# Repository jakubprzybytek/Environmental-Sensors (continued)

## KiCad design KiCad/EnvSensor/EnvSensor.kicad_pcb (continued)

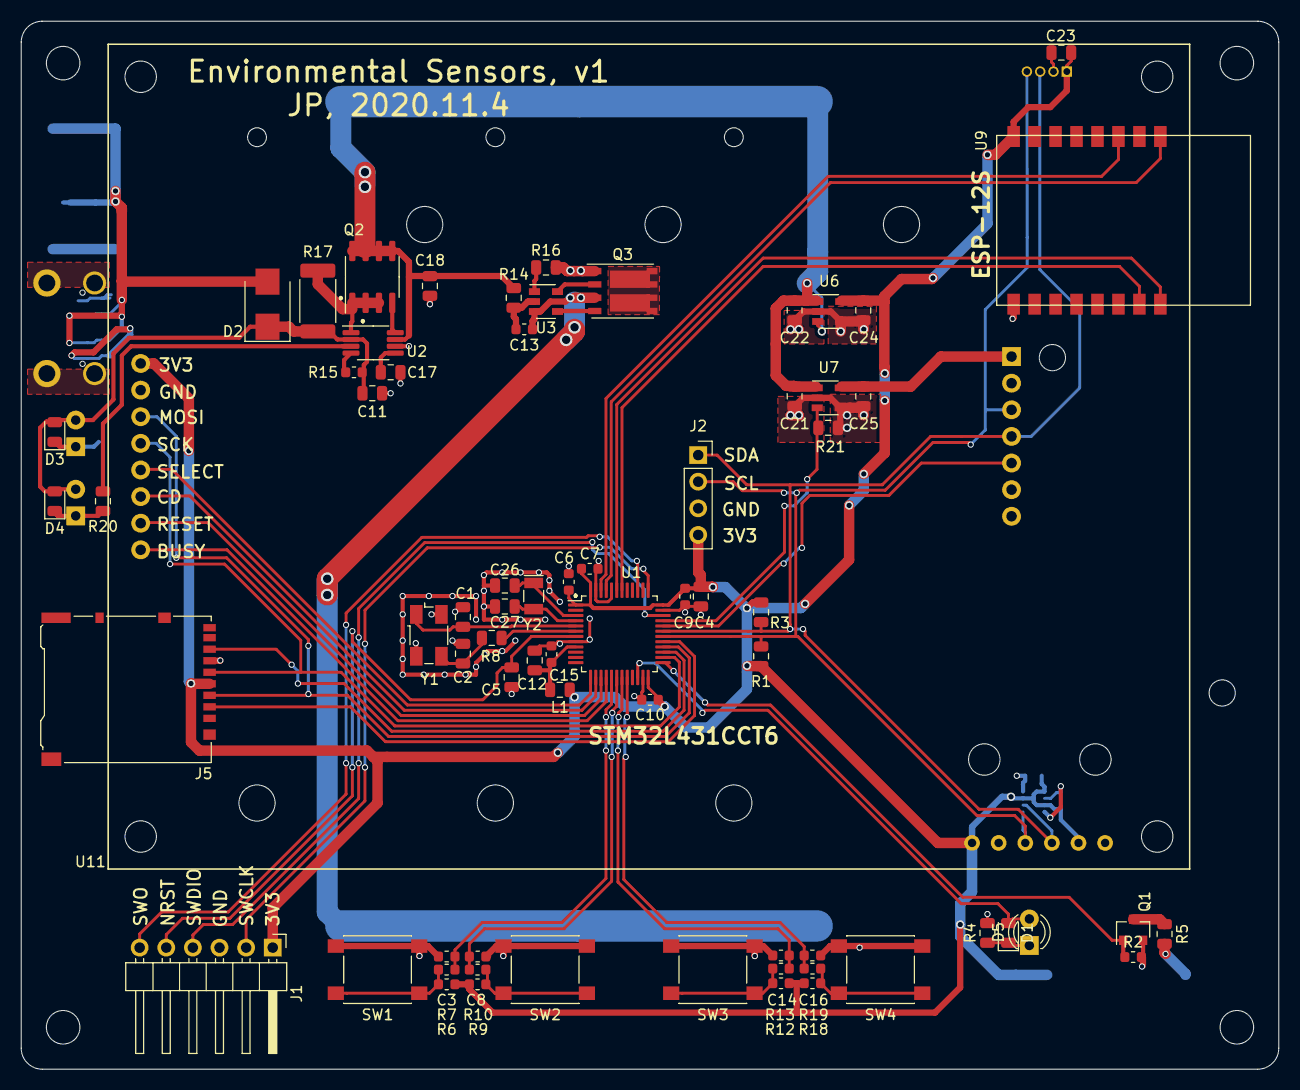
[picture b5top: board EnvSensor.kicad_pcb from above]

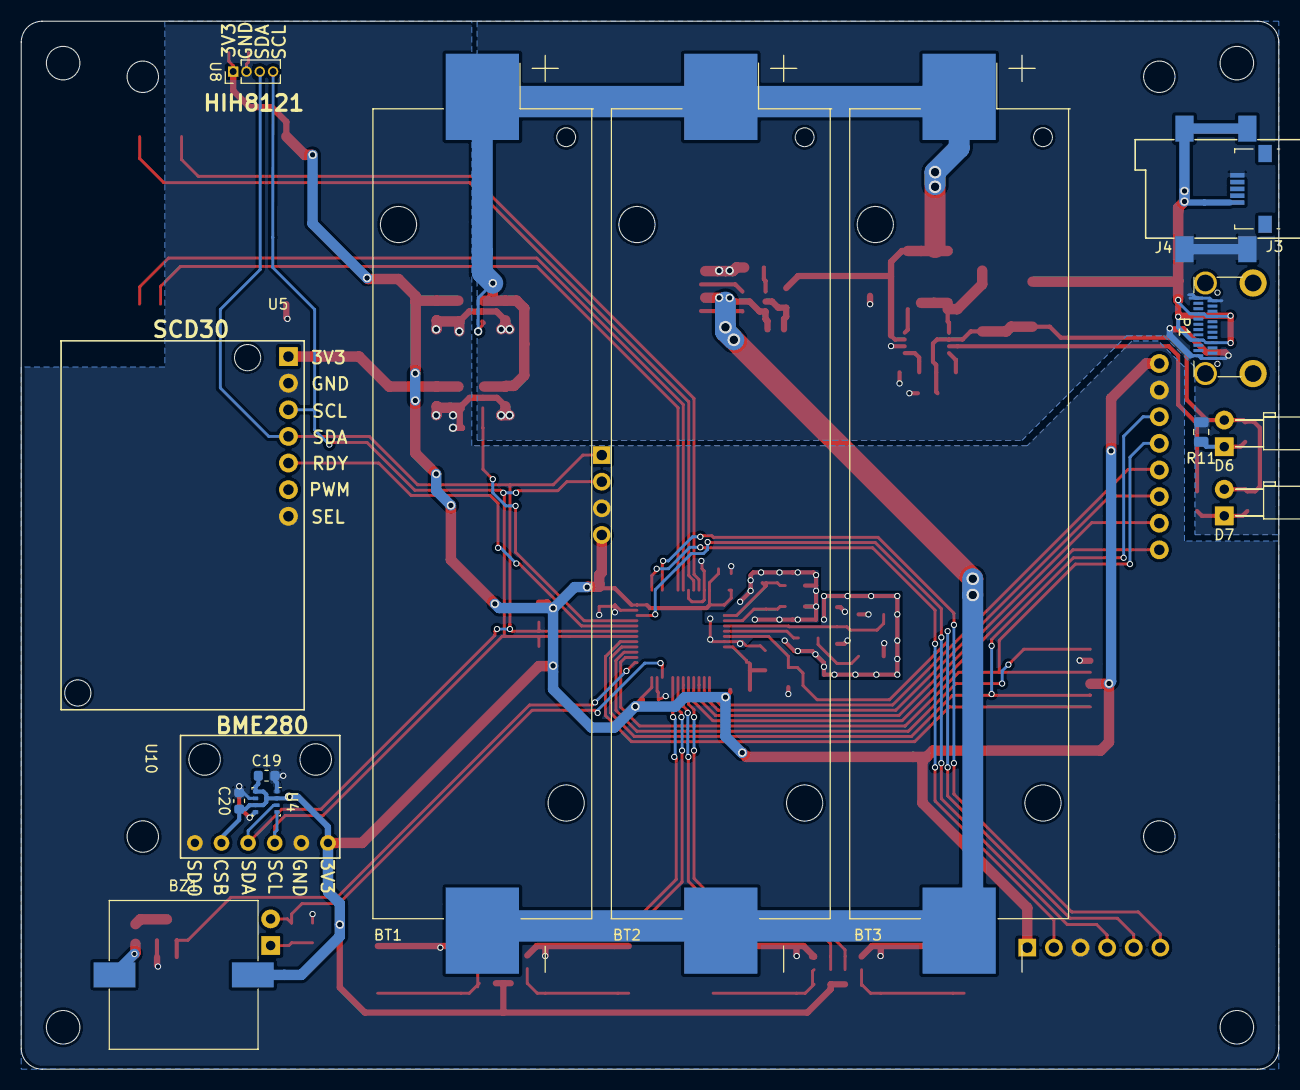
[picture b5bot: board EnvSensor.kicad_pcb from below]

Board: 2 copper layers, 120.0 x 100.0 mm, 90 parts (16 on the bottom side), 58 nets.

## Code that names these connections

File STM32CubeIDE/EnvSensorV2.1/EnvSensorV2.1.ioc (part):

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Mcu.Name=STM32L451R(C-E)Tx
Mcu.Package=LQFP64
Mcu.UserName=STM32L451RETx
PA0.GPIOParameters=GPIO_Label
PA0.GPIO_Label=BATTERY_MEASURE_INPUT
PA0.Signal=ADCx_IN5
PA10.Mode=I2C
PA10.Signal=I2C1_SDA
PA11.GPIOParameters=PinState,GPIO_Label
PA11.GPIO_Label=SDIO_POWER_ENABLE
PA11.PinState=GPIO_PIN_RESET
PA11.Signal=GPIO_Output
PA12.GPIOParameters=GPIO_PuPd,GPIO_Label
PA12.GPIO_Label=SDIO_DETECT
PA12.GPIO_PuPd=GPIO_PULLUP
PA12.Signal=GPIO_Input
PA13\ (JTMS/SWDIO).Mode=Trace_Asynchronous_SW
PA13\ (JTMS/SWDIO).Signal=SYS_JTMS-SWDIO
PA14\ (JTCK/SWCLK).Mode=Trace_Asynchronous_SW
PA14\ (JTCK/SWCLK).Signal=SYS_JTCK-SWCLK
PA2.Mode=Asynchronous
PA2.Signal=USART2_TX
PA3.Mode=Asynchronous
PA3.Signal=USART2_RX
PA5.Mode=TX_Only_Simplex_Unidirect_Master
PA5.Signal=SPI1_SCK
PA7.Mode=TX_Only_Simplex_Unidirect_Master
PA7.Signal=SPI1_MOSI
PA8.GPIOParameters=GPIO_Label
PA8.GPIO_Label=SCD30_READY
PA8.Signal=GPXTI8
PA9.Mode=I2C
PA9.Signal=I2C1_SCL
PB0.GPIOParameters=GPIO_Label
PB0.GPIO_Label=E_INK_RESET
PB0.Signal=GPIO_Output
PB1.GPIOParameters=GPIO_Label
PB1.GPIO_Label=E_INK_BUSY
PB1.Signal=GPXTI1
PB12.GPIOParameters=GPIO_Label
PB12.GPIO_Label=SWITCH_1
PB12.Signal=GPXTI12
PB13.GPIOParameters=GPIO_Label
PB13.GPIO_Label=SWITCH_2
PB13.Signal=GPXTI13
PB14.GPIOParameters=GPIO_Label
PB14.GPIO_Label=SWITCH_3
PB14.Signal=GPXTI14
PB15.GPIOParameters=GPIO_Label
PB15.GPIO_Label=SWITCH_4
PB15.Signal=GPXTI15
PB2.GPIOParameters=PinState,GPIO_Label
PB2.GPIO_Label=POWER_5V_ENABLE
PB2.PinState=GPIO_PIN_RESET
PB2.Signal=GPIO_Output
PB3\ (JTDO/TRACESWO).Mode=Trace_Asynchronous_SW
PB3\ (JTDO/TRACESWO).Signal=SYS_JTDO-SWO
PC0.GPIOParameters=GPIO_Label
PC0.GPIO_Label=LED_4
PC0.Signal=GPIO_Output
PC1.GPIOParameters=GPIO_Label
PC1.GPIO_Label=LED_3
PC1.Signal=GPIO_Output
PC10.GPIOParameters=GPIO_PuPd,GPIO_Speed_High_Default
PC10.GPIO_PuPd=GPIO_PULLUP
PC10.GPIO_Speed_High_Default=GPIO_SPEED_FREQ_LOW
PC10.Mode=SD_4_bits_Wide_bus
PC10.Signal=SDMMC1_D2
PC11.GPIOParameters=GPIO_PuPd,GPIO_Speed_High_Default
PC11.GPIO_PuPd=GPIO_PULLUP
PC11.GPIO_Speed_High_Default=GPIO_SPEED_FREQ_LOW
PC11.Mode=SD_4_bits_Wide_bus
PC11.Signal=SDMMC1_D3
PC12.GPIOParameters=GPIO_Speed_High_Default
PC12.GPIO_Speed_High_Default=GPIO_SPEED_FREQ_LOW
PC12.Mode=SD_4_bits_Wide_bus
PC12.Signal=SDMMC1_CK
PC14-OSC32_IN\ (PC14).Mode=LSE-External-Oscillator
PC14-OSC32_IN\ (PC14).Signal=RCC_OSC32_IN
PC15-OSC32_OUT\ (PC15).Mode=LSE-External-Oscillator
PC15-OSC32_OUT\ (PC15).Signal=RCC_OSC32_OUT
PC2.GPIOParameters=GPIO_Label
PC2.GPIO_Label=LED_2
PC2.Signal=GPIO_Output
PC3.GPIOParameters=GPIO_Label
PC3.GPIO_Label=LED_1
PC3.Signal=GPIO_Output
PC4.GPIOParameters=GPIO_Label
PC4.GPIO_Label=E_INK_SELECT
PC4.Signal=GPIO_Output
PC5.GPIOParameters=GPIO_Speed,GPIO_Label
PC5.GPIO_Label=E_INK_DC
PC5.GPIO_Speed=GPIO_SPEED_FREQ_HIGH
PC5.Signal=GPIO_Output
PC6.GPIOParameters=GPIO_Label
PC6.GPIO_Label=BATTERY_MEASURE_ENABLE
PC6.Signal=GPIO_Output
PC8.GPIOParameters=GPIO_Speed_High_Default
PC8.GPIO_Speed_High_Default=GPIO_SPEED_FREQ_LOW
PC8.Mode=SD_4_bits_Wide_bus
PC8.Signal=SDMMC1_D0
PC9.GPIOParameters=GPIO_Speed_High_Default
PC9.GPIO_Speed_High_Default=GPIO_SPEED_FREQ_LOW
PC9.Mode=SD_4_bits_Wide_bus
PC9.Signal=SDMMC1_D1
PD2.GPIOParameters=GPIO_PuPd,GPIO_Speed_High_Default
PD2.GPIO_PuPd=GPIO_PULLUP
PD2.GPIO_Speed_High_Default=GPIO_SPEED_FREQ_LOW
PD2.Mode=SD_4_bits_Wide_bus
PD2.Signal=SDMMC1_CMD
PH0-OSC_IN\ (PH0).Mode=HSE-External-Oscillator
PH0-OSC_IN\ (PH0).Signal=RCC_OSC_IN
PH1-OSC_OUT\ (PH1).Mode=HSE-External-Oscillator
PH1-OSC_OUT\ (PH1).Signal=RCC_OSC_OUT
RCC.HSE_VALUE=16000000
RCC.SYSCLKFreq_VALUE=16000000
RCC.SYSCLKSource=RCC_SYSCLKSOURCE_HSE
board=custom

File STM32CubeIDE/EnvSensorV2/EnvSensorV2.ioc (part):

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Mcu.Name=STM32L451R(C-E)Tx
Mcu.Package=LQFP64
Mcu.UserName=STM32L451RCTx
PA0.GPIOParameters=GPIO_Label
PA0.GPIO_Label=BATTERY_MEASURE_INPUT
PA0.Signal=ADCx_IN5
PA1.Signal=GPIO_Analog
PA10.Mode=I2C
PA10.Signal=I2C1_SDA
PA13\ (JTMS/SWDIO).Mode=Trace_Asynchronous_SW
PA13\ (JTMS/SWDIO).Signal=SYS_JTMS-SWDIO
PA14\ (JTCK/SWCLK).Mode=Trace_Asynchronous_SW
PA14\ (JTCK/SWCLK).Signal=SYS_JTCK-SWCLK
PA2.Mode=Asynchronous
PA2.Signal=USART2_TX
PA3.Mode=Asynchronous
PA3.Signal=USART2_RX
PA5.Mode=TX_Only_Simplex_Unidirect_Master
PA5.Signal=SPI1_SCK
PA7.Mode=TX_Only_Simplex_Unidirect_Master
PA7.Signal=SPI1_MOSI
PA8.GPIOParameters=GPIO_PuPd,GPIO_Label
PA8.GPIO_Label=SCD30_READY
PA8.GPIO_PuPd=GPIO_NOPULL
PA8.Signal=GPXTI8
PA9.Mode=I2C
PA9.Signal=I2C1_SCL
PB0.GPIOParameters=GPIO_Label
PB0.GPIO_Label=E_INK_RESET
PB0.Signal=GPIO_Output
PB1.GPIOParameters=GPIO_Label
PB1.GPIO_Label=E_INK_BUSY
PB1.Signal=GPXTI1
PB12.GPIOParameters=GPIO_Label
PB12.GPIO_Label=SWITCH_1
PB12.Signal=GPXTI12
PB13.GPIOParameters=GPIO_Label
PB13.GPIO_Label=SWITCH_2
PB13.Signal=GPXTI13
PB14.GPIOParameters=GPIO_Label
PB14.GPIO_Label=SWITCH_3
PB14.Signal=GPXTI14
PB15.GPIOParameters=GPIO_Label
PB15.GPIO_Label=SWITCH_4
PB15.Signal=GPXTI15
PB2.GPIOParameters=PinState,GPIO_Label
PB2.GPIO_Label=POWER_5V_ENABLE
PB2.PinState=GPIO_PIN_SET
PB2.Signal=GPIO_Output
PB3\ (JTDO/TRACESWO).Mode=Trace_Asynchronous_SW
PB3\ (JTDO/TRACESWO).Signal=SYS_JTDO-SWO
PB5.GPIOParameters=GPIO_Label
PB5.GPIO_Label=BATTERY_MEASURE_ENABLE
PB5.Signal=GPIO_Output
PB6.Signal=GPIO_Analog
PB8.GPIOParameters=GPIO_Label
PB8.GPIO_Label=SDIO_DETECT
PB8.Signal=GPIO_Input
PB9.GPIOParameters=GPIO_Label
PB9.GPIO_Label=SDIO_POWER_ENABLE
PB9.Signal=GPIO_Output
PC0.GPIOParameters=GPIO_Label
PC0.GPIO_Label=LED_4
PC0.Signal=GPIO_Output
PC1.GPIOParameters=GPIO_Label
PC1.GPIO_Label=LED_3
PC1.Signal=GPIO_Output
PC10.Mode=SD_4_bits_Wide_bus
PC10.Signal=SDMMC1_D2
PC11.Mode=SD_4_bits_Wide_bus
PC11.Signal=SDMMC1_D3
PC12.Mode=SD_4_bits_Wide_bus
PC12.Signal=SDMMC1_CK
PC2.GPIOParameters=GPIO_Label
PC2.GPIO_Label=LED_2
PC2.Signal=GPIO_Output
PC3.GPIOParameters=GPIO_Label
PC3.GPIO_Label=LED_1
PC3.Signal=GPIO_Output
PC4.GPIOParameters=GPIO_Label
PC4.GPIO_Label=E_INK_SELECT
PC4.Signal=GPIO_Output
PC5.GPIOParameters=GPIO_Speed,GPIO_Label
PC5.GPIO_Label=E_INK_DC
PC5.GPIO_Speed=GPIO_SPEED_FREQ_HIGH
PC5.Signal=GPIO_Output
PC8.Mode=SD_4_bits_Wide_bus
PC8.Signal=SDMMC1_D0
PC9.Mode=SD_4_bits_Wide_bus
PC9.Signal=SDMMC1_D1
PD2.Mode=SD_4_bits_Wide_bus
PD2.Signal=SDMMC1_CMD
PH0-OSC_IN\ (PH0).Mode=HSE-External-Oscillator
PH0-OSC_IN\ (PH0).Signal=RCC_OSC_IN
PH1-OSC_OUT\ (PH1).Mode=HSE-External-Oscillator
PH1-OSC_OUT\ (PH1).Signal=RCC_OSC_OUT
RCC.HSE_VALUE=16000000
board=custom

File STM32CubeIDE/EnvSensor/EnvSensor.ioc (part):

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Mcu.Name=STM32L431C(B-C)Tx
Mcu.Package=LQFP48
Mcu.UserName=STM32L431CCTx
PA10.Mode=I2C
PA10.Signal=I2C1_SDA
PA11.GPIOParameters=GPIO_Label
PA11.GPIO_Label=SCD30_Ready
PA11.Signal=GPIO_Input
PA12.GPIOParameters=GPIO_Label
PA12.GPIO_Label=AuxPowerEnable
PA12.Signal=GPIO_Output
PA13\ (JTMS-SWDIO).Mode=Trace_Asynchronous_SW
PA13\ (JTMS-SWDIO).Signal=SYS_JTMS-SWDIO
PA14\ (JTCK-SWCLK).Mode=Trace_Asynchronous_SW
PA14\ (JTCK-SWCLK).Signal=SYS_JTCK-SWCLK
PA3.GPIOParameters=PinState,GPIO_Label
PA3.GPIO_Label=E-INK_Select
PA3.PinState=GPIO_PIN_SET
PA3.Signal=GPIO_Output
PA4.GPIOParameters=GPIO_Label
PA4.GPIO_Label=E-INK_DC
PA4.Signal=GPIO_Output
PA5.GPIOParameters=PinState,GPIO_Label
PA5.GPIO_Label=E-INK_Reset
PA5.PinState=GPIO_PIN_RESET
PA5.Signal=GPIO_Output
PA6.GPIOParameters=GPIO_Label
PA6.GPIO_Label=E-INK_Busy
PA6.Signal=GPXTI6
PA7.GPIOParameters=GPIO_Label,GPIO_ModeDefaultEXTI
PA7.GPIO_Label=Switch1
PA7.GPIO_ModeDefaultEXTI=GPIO_MODE_IT_FALLING
PA7.Signal=GPXTI7
PA8.GPIOParameters=PinState,GPIO_Label
PA8.GPIO_Label=SD_Select
PA8.PinState=GPIO_PIN_SET
PA8.Signal=GPIO_Output
PA9.Mode=I2C
PA9.Signal=I2C1_SCL
PB0.GPIOParameters=GPIO_Label,GPIO_ModeDefaultEXTI
PB0.GPIO_Label=Switch2
PB0.GPIO_ModeDefaultEXTI=GPIO_MODE_IT_FALLING
PB0.Signal=GPXTI0
PB1.GPIOParameters=GPIO_Label,GPIO_ModeDefaultEXTI
PB1.GPIO_Label=Switch3
PB1.GPIO_ModeDefaultEXTI=GPIO_MODE_IT_FALLING
PB1.Signal=GPXTI1
PB11.GPIOParameters=GPIO_Label
PB11.GPIO_Label=LED
PB11.Signal=GPIO_Output
PB12.GPIOParameters=GPIO_Label
PB12.GPIO_Label=Buzzer
PB12.Signal=GPIO_Output
PB13.Mode=Full_Duplex_Master
PB13.Signal=SPI2_SCK
PB14.Mode=Full_Duplex_Master
PB14.Signal=SPI2_MISO
PB15.Mode=Full_Duplex_Master
PB15.Signal=SPI2_MOSI
PB2.GPIOParameters=GPIO_Label,GPIO_ModeDefaultEXTI
PB2.GPIO_Label=Switch4
PB2.GPIO_ModeDefaultEXTI=GPIO_MODE_IT_FALLING
PB2.Signal=GPXTI2
PB3\ (JTDO-TRACESWO).Mode=Trace_Asynchronous_SW
PB3\ (JTDO-TRACESWO).Signal=SYS_JTDO-SWO
PB6.Mode=Asynchronous
PB6.Signal=USART1_TX
PB7.Mode=Asynchronous
PB7.Signal=USART1_RX
PC14-OSC32_IN\ (PC14).Mode=LSE-External-Oscillator
PC14-OSC32_IN\ (PC14).Signal=RCC_OSC32_IN
PC15-OSC32_OUT\ (PC15).Mode=LSE-External-Oscillator
PC15-OSC32_OUT\ (PC15).Signal=RCC_OSC32_OUT
RCC.HSE_VALUE=8000000
RCC.SYSCLKFreq_VALUE=16000000
RCC.SYSCLKSource=RCC_SYSCLKSOURCE_HSI
board=custom

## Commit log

2020-10-06 init
2020-10-09 Schematic done
2020-10-30 Some commit
2020-11-04 Last pcb fixes
2020-12-22 eInk initial code
2020-12-22 TouchGFX and BMP280 code added
2020-12-22 'clean'
2020-12-23 Screen improvements
2020-12-23 Screen refactoring
2020-12-23 Speaker added. Tweaks in screen
2020-12-23 Faster eInk display transfer, faster I2C
2020-12-27 SCD30 code added
2020-12-29 scd work
2020-12-29 scd30 more work
2020-12-29 Files renamed
2020-12-29 Docs added for SCD30
2020-12-29 Small tweaks
2020-12-30 Sleep mode introduced
2021-01-01 Single buffer fix. Retry code'
2021-01-02 Display communication is now asynchronious
2021-01-04 RTC for refreshing display
2021-01-04 Font sizes tweaks. Clean is now faster
2021-01-04 bmp280 intrval set to 4s
2021-01-04 Delay during display refresh removed
2021-01-04 Display refresh is now better protected
2021-01-06 Stopping clocks when sleep
2021-01-07 Vdd readout routine added
2021-01-10 Switched to 4.2 A module
2021-01-10 4.2 eInk switched to gray2 mode
2021-01-10 Clean up
2021-01-15 Small display refactor. SD routine init
2021-01-15 Vdd readout refactor
2021-01-15 Displaying sd available space
2021-01-15 Displaying info about sd errors
2021-01-16 Logger refactor
2021-01-16 More Logger refactor
2021-01-16 Logging time now
2021-01-16 Missing vdd and sd info bug fixed
2021-01-19 Screen controllers introduced
2021-01-19 Settings screen development
2021-01-19 Screen folder refactored
2021-01-19 Screen refactored
2021-01-20 Screen refactor
2021-01-20 More screen refactor
2021-01-20 Displaying date and time
2021-01-21 Updating date and time
2021-01-22 Minor tweaks
2021-01-23 Free memory code moved to FileSystem
2021-01-26 Charts view introduced
2021-01-26 Minor refactor
2021-01-26 Memory leak bug fixed
2021-01-27 EnvState csf formatter extracted
2021-02-03 Charts code
2021-02-04 Chart loader fixes
2021-02-05 More on chart
2021-02-08 Logger is now disabled on start up
2021-02-08 Readout moved
2021-02-08 Led blinking changed
2021-02-10 Time bug fixed
2021-03-12 3d prints. Main screen amended. Last bar issue fixed
2021-09-05 last fixes
2021-09-30 New PCB
2021-10-04 Work on pcb v2
2021-10-30 Finishing touches
2021-11-17 pcb finishing touches
2021-11-23 Finishing
2021-12-06 Optimising ground pane
2021-12-07 Gerbers
2022-01-24 STM32CubeIDE/EnvSensorV2 introduced
2022-01-26 sensors work
2022-01-29 bme280
2022-01-29 Pressure, temp, humidity code clean up
2022-01-29 Removing unused pins, htpma115c0
2022-01-30 Particles sensor
2022-02-08 SDMMC and SPI enabled
2022-02-08 pcb updates
2022-02-26 touchgfx introduced
2022-02-27 Implementing display
2022-02-27 touchgfx work
2022-02-27 temp and pressure
2022-06-11 forgotten commit
2022-06-11 gitignore
2022-06-11 Refactor: moving to utils folder
2022-06-11 Blinking leds extracted
2022-06-11 TempPressureSensor into class
2022-11-11 Upgarding CubeIDE Making mutext static
2022-11-11 All queues are now static
2022-11-13 Tiny fixes
2022-11-13 BME readouts debug log refactor
2022-11-13 CO2 sensor refactoring
2022-11-13 Tiny refactor
2022-11-13 Retries added
2022-11-13 Retries added to co2 sensor
2022-11-14 VoltageSensor introduced
2022-11-15 VoltageSensor. DisplayController
2022-11-17 Static thread allocation
2022-11-17 Voltage readout in state
2022-11-17 TouchGFX upgrade to 4.20.0 and Voltage Container
2022-11-17 TouchGFX upgrade in STM32CubeIDE
2022-11-17 DisplayCommands introduced
2022-11-17 Simple timer
2022-11-17 Default thread stack optimised
2022-11-19 Flushing frame buffer through Display Controller
2022-11-19 missing file
2022-11-28 Initial 2.1 commit
2022-11-29 rescue
2022-12-03 poznan commit
2022-12-14 pcb started
2022-12-20 More pcb work
2022-12-28 more work
2023-04-02 Upgrade to STM32CubeIDE 1.12
2023-04-02 CPU led and Display led introduced
2023-04-02 Model refactor
2023-04-03 Better tracing of display transmition
2023-04-03 rounding readouts before displaying
2023-04-05 RTC introduced
2023-04-08 Final PCB work
2023-04-08 Main pcb
2023-04-12 Main PCB work
2023-04-22 Main work done on PCB
2023-04-22 TouchGFx upgrade 4.21.3
2023-04-22 .gitignore updated
2023-04-22 UI tweaks
2023-04-23 DateTime HardFault issue worked around
2023-04-25 Refactor
2023-04-25 More logging
2023-04-25 Stack size tweaks
2023-04-27 FatFS introduced
2023-04-29 Rename
2023-05-01 PCB work
2023-05-05 Particles sensor refactor
2023-05-05 External oscillator enabled
2023-05-06 hpma pinout
2023-05-06 STM32CubeIDE upgrade
2023-05-11 TouchGFX upgrade, particles container
2023-05-14 Ability to stop PerticlesSensor
2023-05-14 Power 5V management moved from HPA device to ParticlesSensor class
2023-05-15 Start and stop particles sensos
2023-05-15 Refactor in DebugLog
2023-05-15 .gitignore fixes
2023-05-15 restore text.xml files
2023-05-15 Final save
2023-05-15 Button label added
2023-05-20 New label in gui. Refactor of synchronisation code in particles sensor
2023-05-20 Paticles sensor - timings adjusted
2023-06-04 Temp I2C sync disabled
2023-06-04 Logging improvements
2023-06-04 More logging in display
2023-06-04 Timer renamed to SensorsController
2023-06-04 Low and high measurements routine
2023-06-04 Moving sensors initialization into SensorsController
2023-06-04 RCT enabled, co2 semaphor replaced with flag
2023-06-04 Removed old co2 semapthore
2023-06-09 Synchronising on display using interrupt
2023-06-16 SOme fixes
2023-06-16 EPD 4in2 code changed. Timing logging in display controller
2023-06-18 Rename readme.txt to ReadMe.md
2023-06-19 Failing Stop Auto Send command doesn't stop sensor now
2023-08-31 Missing assignements fixed
2023-08-31 fixes
2023-09-06 Finishing touhches on main board
2024-02-03 LM2735 fixes
2024-03-03 More fixes
2024-06-16 Bore moving swd and i2c
2024-06-23 Before moving i2c tracks
2024-08-01 Finish
2024-09-21 c++ project for 2.1 introduced
2024-09-21 Small screen introduced
2024-09-22 HSE enabled
2024-09-26 'touchgfx'
2024-09-26 'rtc'
2024-09-29 hpma
2024-10-06 attempt to sd card
2024-10-14 sd card using SPI
2024-10-19 SD card using sdmmc
2024-10-20 logging
2024-10-24 App controllers
2024-10-26 Bottom Buttons
2024-10-30 Controller
2024-11-06 Time setting
2024-11-06 Making queues dynamic
2024-11-08 Leds
2024-11-09 Charts
2024-11-09 Buttons and leds
2024-11-15 some work
2024-11-15 Ignoring 0 values
2024-11-15 6 hours interval introduced
2024-11-21 Scalled y axis
2024-11-21 Additional backround invalidation
2024-11-22 Tweaks
2024-11-22 Particles chart
2024-12-08 HPMA Tweaks
2024-12-12 Particles Sensor tweaks
2024-12-14 Changing BME280 mode to forced and take measurements every 2mins
2024-12-14 CO2 sensor tweaks
2024-12-14 Controller events refactor
2025-01-19 Delayed refresh refactored.
2025-01-19 Inactivity screen timeout
2025-01-24 Sensors can be stopped and resumed
2025-01-24 Setting ui controller refactor
2025-01-26 Batt indicators. Empty battery screen.
2025-01-26 Displaying date and time. 'No data' bug fixed.
2025-01-30 Final touches
2025-02-04 Release profile fixes
2025-02-15 Last stuff
